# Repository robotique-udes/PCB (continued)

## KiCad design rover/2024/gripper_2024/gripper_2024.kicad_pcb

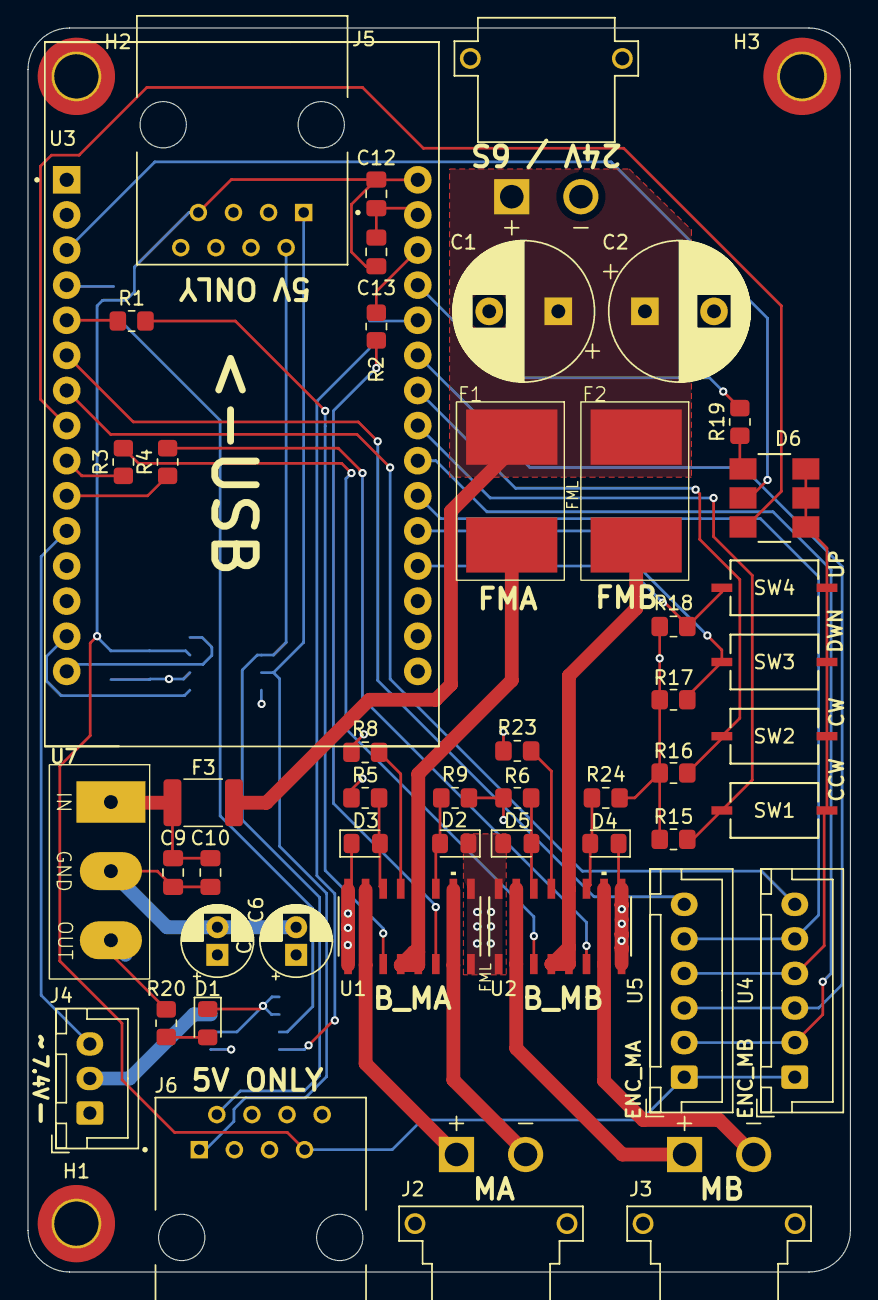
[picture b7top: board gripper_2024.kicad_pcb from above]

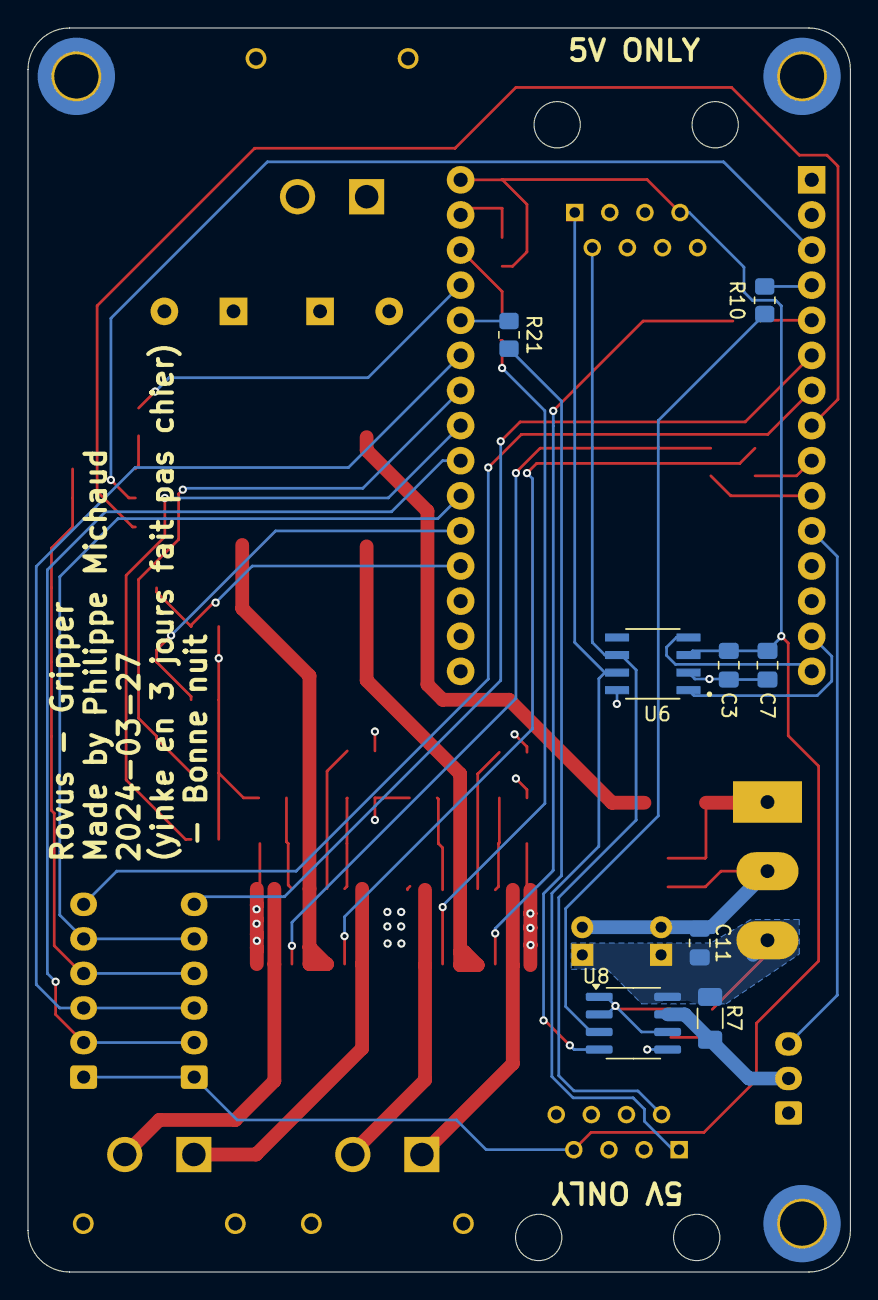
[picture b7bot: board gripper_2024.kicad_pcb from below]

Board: 4 copper layers, 59.5 x 90.0 mm, 60 parts (8 on the bottom side), 50 nets.

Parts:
C1, C2: 470uf; CP_Radial_D10.0mm_P5.00mm
C3, C9: 100nf; C_0805_2012Metric_Pad1.18x1.45mm_HandSolder
C6, C8: 100uF; CP_Radial_D5.0mm_P2.00mm
C7, C10, C13: 10uF; C_0805_2012Metric_Pad1.18x1.45mm_HandSolder
C11, C12: 100nF; C_0805_2012Metric_Pad1.18x1.45mm_HandSolder
D1: LED GREEN; LED_0805_2012Metric_Pad1.15x1.40mm_HandSolder
D2, D3, D4, D5: R; LED_0805_2012Metric_Pad1.15x1.40mm_HandSolder
D6: CLP6C-FKB-CKNPRGJBB7A363; CLP6C-FKB-CKNPRGJBB7A363_CRE
F1, F2: 4A; 3425L200_60MR
F3: 1.5A; Fuse_1812_4532Metric_Pad1.30x3.40mm_HandSolder
H1, H2, H3: MountingHole_Pad; MountingHole_3.2mm_M3_DIN965_Pad_TopBottom
J1: XT30PW-M; AMASS_XT30PW-M
J2, J3: XT30PW-F; AMASS_XT30PW-F
J4: B3B-XH-A_LF__SN_; JST_XH_B3B-XH-A_1x03_P2.50mm_Vertical
J5, J6: RJ45; AMPHENOL_54601-908WPLF
R1, R2, R3, R4, R5, R20, R23: 1K; R_0805_2012Metric_Pad1.20x1.40mm_HandSolder
R6, R8, R9, R15, R16, R17, R18, R24: 3.3K; R_0805_2012Metric_Pad1.20x1.40mm_HandSolder
R7: 0.010; R_1206_3216Metric_Pad1.30x1.75mm_HandSolder
R10, R21: 0; R_0805_2012Metric_Pad1.20x1.40mm_HandSolder
R19: 68; R_0805_2012Metric_Pad1.20x1.40mm_HandSolder
SW1, SW2, SW3, SW4: TS09-63-25-WT-160-SMT-TR; SW_TS09-63-25_CUD
U1, U2: VNH5200ASTR-E; SO_200AS-E_STM
U3: MODULE_ESP32_DEVKIT_V1
U4, U5: JST_XH_B6B-XH-A_1x06_P2.50mm_Vertical
U6: TJA1050T_CM_118; SOIC127P600X175-8N
U7: REG_7.4V
U8: INA219AxD; SOIC-8_3.9x4.9mm_P1.27mm

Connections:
+3.3V: R6.2, R8.2, R9.1, R15.1, R16.2, R17.2, R18.2, R24.1, U3.1 (3V3), U8.5 (VS)
+5V: C3.1, C7.1, C12.1, C13.1, J5.7, J6.7, U3.30 (VIN), U4.1, U5.1, U6.3 (VCC)
+7.4V: C6.1, C8.1, C11.2, R7.2, R20.1, U7.3 (V_{OUT}), U8.8 (IN+)
+24V: C1.1, C2.1, F1.1, F2.1, F3.1, J1.P
CANH: J5.1, J6.1, U6.7 (CANH)
CANL: J5.2, J6.2, U6.6 (CANL)
CS_Poignet: U3.7 (TX2), U4.6
CS_Rotation: U3.6 (RX2), U5.6
GND: C1.2, C2.2, C3.2, C6.2, C7.2, C8.2, C9.2, C10.2, C11.1, C12.2, C13.2, D1.1 (K), D2.1 (K), D3.1 (K), D4.1 (K), D5.1 (K), D6.4, D6.5, D6.6, H1.1, H2.1, H3.1, J1.N, J4.1, J5.8, J6.8, R5.2, R23.2, SW1.1, SW2.1, SW3.1, SW4.1, U1.1 (GNDA), U1.8 (GNDB), U1.9 (GNDB), U1.16 (GNDA), U2.1 (GNDA), U2.8 (GNDB), U2.9 (GNDB), U2.16 (GNDA), U3.2 (GND), U4.4, U5.4, U6.2 (GND), U6.8 (S), U7.2 (GND), U8.1 (A1), U8.2 (A0), U8.6 (GND)
LED_B: D6.3, U3.8 (D5)
LED_G: D6.2, U3.3 (D15)
LED_R: R19.2, U3.27 (D12)
MA+: J2.P, U1.2 (OUTA), U1.15 (OUTA)
MA-: J2.N, U1.7 (OUTB), U1.10 (OUTB)
MA_24V: F1.2, U1.4 (VCC), U1.5 (VCC), U1.12 (VCC)
MA_S1: R1.1, U3.5 (D4)
MA_S2: R2.1, U3.28 (D13)
MB+: J3.P, U2.2 (OUTA), U2.15 (OUTA)
MB-: J3.N, U2.7 (OUTB), U2.10 (OUTB)
MB_24V: F2.2, U2.4 (VCC), U2.5 (VCC), U2.12 (VCC)
MB_S1: R3.1, U3.9 (D18)
MB_S2: R4.1, U3.10 (D19)
MISO: U3.21 (D32), U4.5, U5.5
MOSI: U3.25 (D27), U4.3, U5.3
unnamed: D1.2 (A), R20.2
unnamed: D2.2 (A), R9.2, U1.11 (ENB/DIAGB)
unnamed: D3.2 (A), R8.1, U1.14 (ENA/DIAGB)
unnamed: D4.2 (A), R24.2, U2.11 (ENB/DIAGB)
unnamed: D5.2 (A), R6.1, U2.14 (ENA/DIAGB)
unnamed: D6.1, R19.1
unnamed: R5.1, U1.13 (CS)
unnamed: R1.2, U1.3 (INA)
unnamed: R2.2, U1.6 (INB)
unnamed: R23.1, U2.13 (CS)
unnamed: R3.2, U2.3 (INA)
unnamed: R4.2, U2.6 (INB)
unnamed: R10.2, U3.4 (D2)
unnamed: R21.2, U3.26 (D14)
unnamed: C9.1, C10.1, F3.2, U7.1 (V_{IN})
PB_POIGNET_FWD: R15.2, SW1.2, U3.23 (D25)
PB_POIGNET_REV: R16.1, SW2.2, U3.24 (D26)
PB_ROT_FWD: R17.1, SW3.2, U3.20 (D35)
PB_ROT_REV: R18.1, SW4.2, U3.19 (D34)
RXC: U3.14 (D22), U6.1 (TXD)
SCK: U3.22 (D33), U4.2, U5.2
SCL: R21.1, U8.4 (SCL)
SDA: R10.1, U8.3 (SDA)
SERVO_POW: J4.2, R7.1, U8.7 (IN-)
SERVO_PWM: J4.3, U3.11 (D21)
TXC: U3.15 (D23), U6.4 (RXD)
